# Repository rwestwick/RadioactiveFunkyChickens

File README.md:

# RadioactiveFunkyChickens

These are the Python files for the RadioactiveFunkyChickens team's PiWars robot.

## Files

### Challenge code

- LineFollowingAlgorithm.py: Code for the [line following challenge] (http://piwars.org/2017-competition/challenges/line-following/)
- MinimalMazeAlgorithm.py: Code for the [Minimal Maze challenge (http://piwars.org/2017-competition/challenges/minimal-maze/)
- straightLineSpeedTest2.py: Code for the [straight line speed test challenge] (http://piwars.org/2017-competition/challenges/straight-line-speed-test/)
- WiimoteControllerNunchukEye.py: Remote controller code to the non-autonomous PiWars challenges. Needs Wiimote Nunchuck and can control the servos for pan and tilt.

### Initio code

Several of the Python files are downloaded from the 4tronix web site to work with the Initio and Robohat hardware.

## See Also

- [RadioactiveFunkyChickens Blog] (https://radioactivefunkychickens.wordpress.com/)
- [PiWars] (http://piwars.org/)
- [Raspberry Pi] (http://www.raspberrypi.org/)
- [4tronix Initio Home Page] (http://4tronix.co.uk/blog/?p=169)

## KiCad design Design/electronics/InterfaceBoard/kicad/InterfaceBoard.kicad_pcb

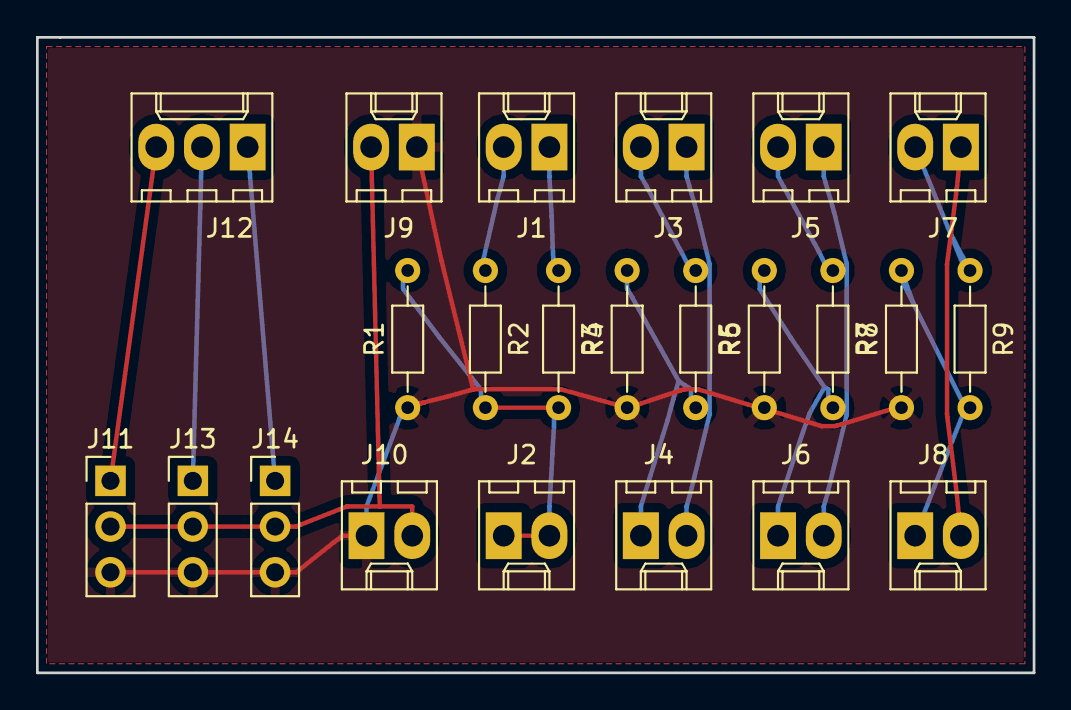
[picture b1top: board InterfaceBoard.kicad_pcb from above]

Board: 2 copper layers, 55.4 x 35.3 mm, 23 parts (0 on the bottom side), 17 nets.

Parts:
J1, J2: PROX1; Molex_KK-6410-02_02x2.54mm_Straight
J3, J4: PROX2; Molex_KK-6410-02_02x2.54mm_Straight
J5, J6: PROX3; Molex_KK-6410-02_02x2.54mm_Straight
J7, J8: PROX4; Molex_KK-6410-02_02x2.54mm_Straight
J9: PWR IN; Molex_KK-6410-02_02x2.54mm_Straight
J10: PWR OUT; Molex_KK-6410-02_02x2.54mm_Straight
J11: HORZ; Pin_Header_Straight_1x03_Pitch2.54mm
J12: SERVO_IN; Molex_KK-6410-03_03x2.54mm_Straight
J13: VERT; Pin_Header_Straight_1x03_Pitch2.54mm
J14: FIRE; Pin_Header_Straight_1x03_Pitch2.54mm
R1, R2, R5, R7, R9: 1k; R_Axial_DIN0204_L3.6mm_D1.6mm_P7.62mm_Horizontal
R3, R4, R6, R8: 2k2; R_Axial_DIN0204_L3.6mm_D1.6mm_P7.62mm_Horizontal

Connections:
+5V: J9.2, J10.2, J11.2, J13.2, J14.2
GND: J9.1, J10.1, J11.3, J13.3, J14.3, R1.1, R4.1, R6.1, R8.1
unnamed: J1.1, R3.1
unnamed: J1.2, R2.1
unnamed: J2.1, J2.2, R1.2, R2.2, R3.2
unnamed: J3.1, J4.2
unnamed: J3.2, R5.1
unnamed: J4.1, R4.2, R5.2
unnamed: J5.1, J6.2
unnamed: J5.2, R7.1
unnamed: J6.1, R6.2, R7.2
unnamed: J7.1, J8.2
unnamed: J7.2, R9.1
unnamed: J8.1, R8.2, R9.2
unnamed: J11.1, J12.3
unnamed: J12.1, J14.1
unnamed: J12.2, J13.1

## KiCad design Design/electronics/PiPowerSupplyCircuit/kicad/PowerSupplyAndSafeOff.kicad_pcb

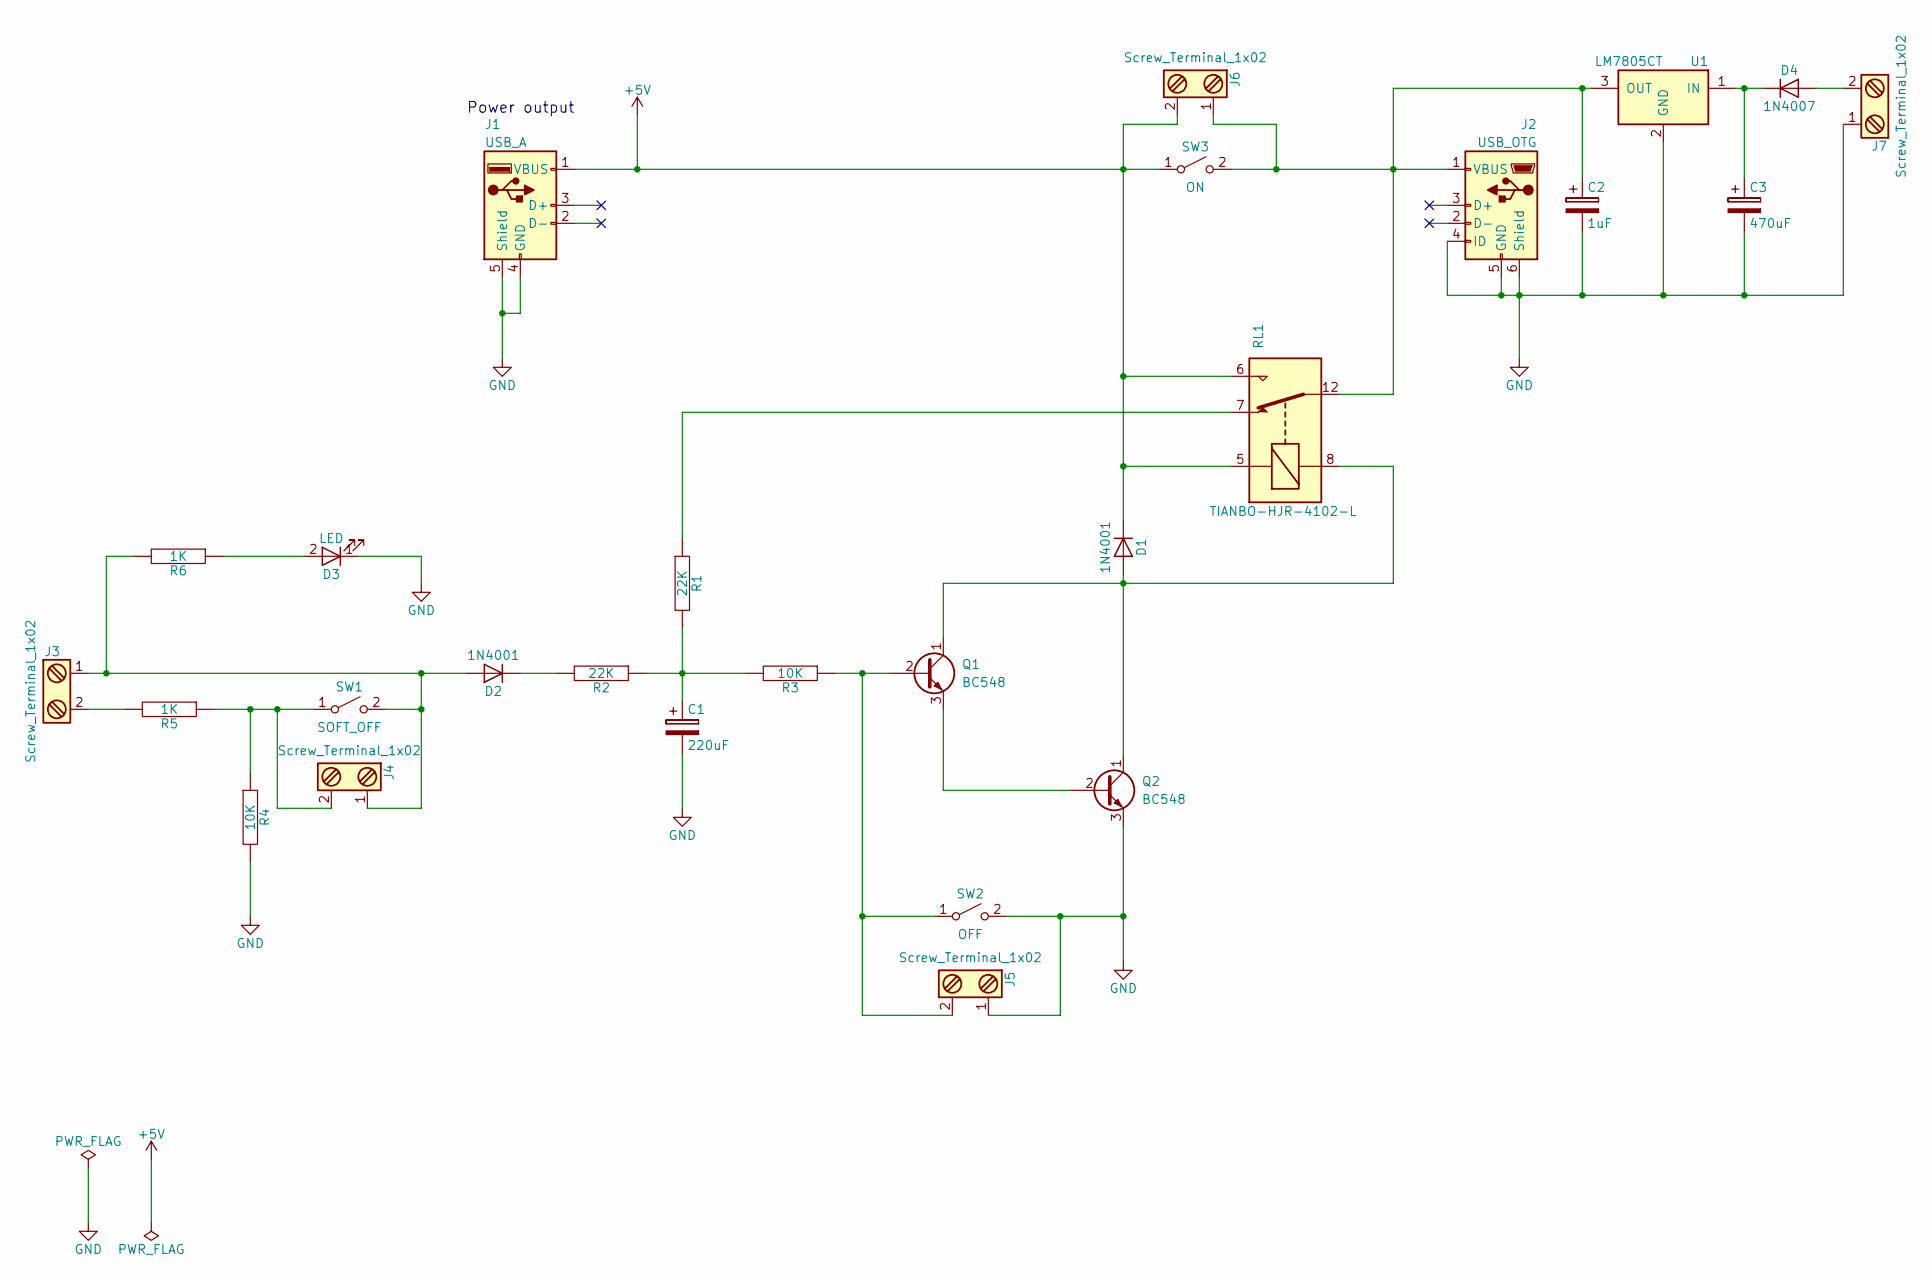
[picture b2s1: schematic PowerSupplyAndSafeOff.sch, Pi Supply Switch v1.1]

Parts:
C1: 220uF; CP_Radial_D5.0mm_P2.50mm
C2: 1uF; CP_Radial_D5.0mm_P2.50mm
C3: 470uF; CP_Radial_D5.0mm_P2.50mm
D1, D2: 1N4001; D_T-1_P10.16mm_Horizontal
D3: LED; LED_D3.0mm
D4: 1N4007; D_T-1_P10.16mm_Horizontal
J1: USB_A
J2: USB_OTG; USB_Micro-B
J3, J4, J5, J6, J7: Screw_Terminal_1x02; PhoenixContact_MC-G_02x5.08mm_Angled
Q1, Q2: BC548; TO-92_Inline_Narrow_Oval
R1, R2: 22K; R_Axial_DIN0207_L6.3mm_D2.5mm_P7.62mm_Horizontal
R3, R4: 10K; R_Axial_DIN0207_L6.3mm_D2.5mm_P7.62mm_Horizontal
R5, R6: 1K; R_Axial_DIN0207_L6.3mm_D2.5mm_P7.62mm_Horizontal
RL1: TIANBO-HJR-4102-L; Relay_SPDT_HJR-4102
SW1: SOFT_OFF; SW_PUSH_6mm_h4.3mm
SW2: OFF; SW_PUSH_6mm_h4.3mm
SW3: ON; SW_PUSH_6mm_h4.3mm
U1: LM7805CT; TO-220

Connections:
+5V: D1.1 (K), J1.1 (VBUS), J6.2, RL1.5, RL1.6, SW3.1 (A)
GND: C1.2, C2.2, C3.2, D3.1 (K), J1.4 (GND), J1.5 (Shield), J2.4 (ID), J2.5 (GND), J2.6 (Shield), J5.1, J7.1, Q2.3 (E), R4.2, SW2.2 (B), U1.2 (GND)
unnamed: C1.1, R1.2, R2.1, R3.2
unnamed: C2.1, J2.1 (VBUS), J6.1, RL1.12, SW3.2 (B), U1.3 (OUT)
unnamed: C3.1, D4.1 (K), U1.1 (IN)
unnamed: D1.2 (A), Q1.1 (C), Q2.1 (C), RL1.8
unnamed: D2.1 (K), R2.2
unnamed: D2.2 (A), J3.1, J4.1, R6.2, SW1.2 (B)
unnamed: D3.2 (A), R6.1
unnamed: D4.2 (A), J7.2
unnamed: J3.2, R5.2
unnamed: J4.2, R4.1, R5.1, SW1.1 (A)
unnamed: J5.2, Q1.2 (B), R3.1, SW2.1 (A)
unnamed: Q1.3 (E), Q2.2 (B)
unnamed: R1.1, RL1.7

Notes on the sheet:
Power output

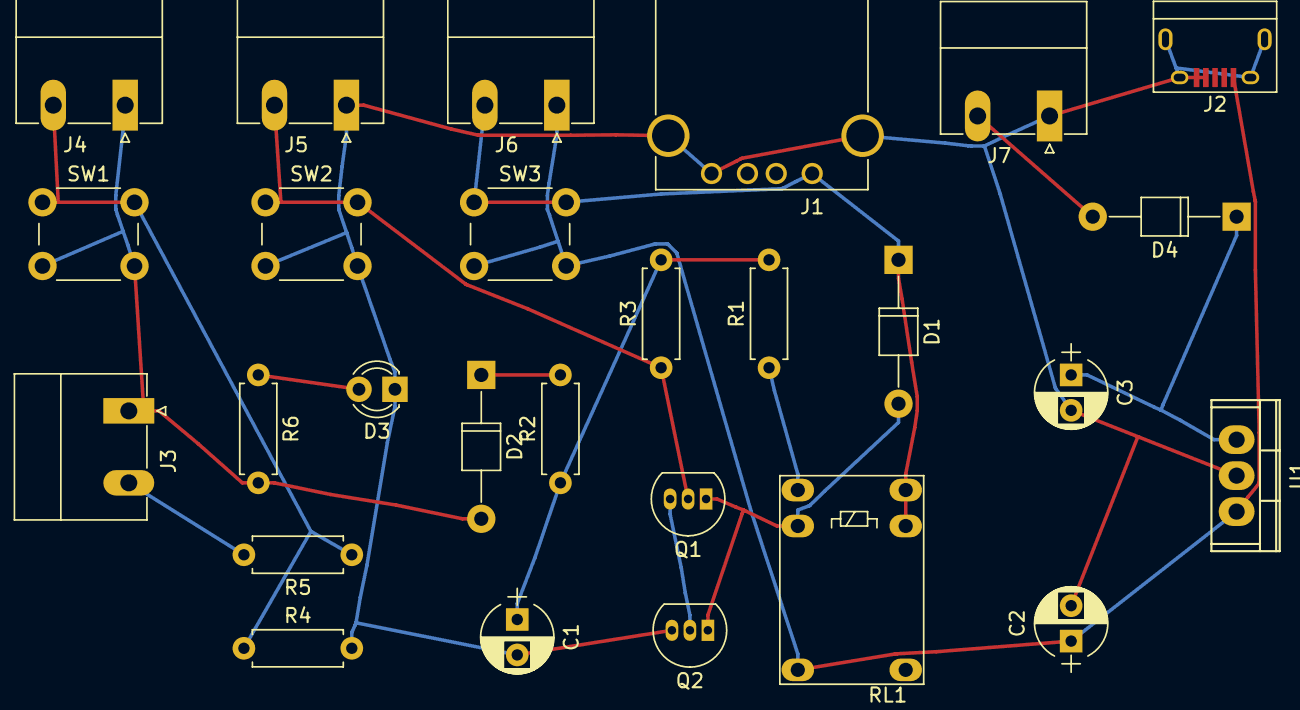
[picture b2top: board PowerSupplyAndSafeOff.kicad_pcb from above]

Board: 2 copper layers, 27 parts (0 on the bottom side), 15 nets.

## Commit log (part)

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2017-02-07 Fixed issues with code following being able to actually run it!
2017-02-07 Moved comment Measurement function to a docstring
2017-02-07 Fixed issues with the LineFollerSensor
2017-02-07 Fixed issues with the ServoController
2017-02-07 Added a one wheel turn (left and right) to the MotorController
2017-02-07 added +x to servod binary
2017-02-08 Made code pep8 compliant using flake8 IRSensor.py LineFollowerSensor.py MotorController.py ServoController.py UltrasonicSensor.py and pylint -f colorized -r no IRSensor.py LineFollowerSensor.py Motor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
2017-02-15 Split out the keyboard key reader into a separate file
2017-02-18 Adding pep8, pylint script for jenkins
2017-02-18 Updated line endings and access rights
2017-02-18 Added pylint config file and updated jenkins script to use it
2017-02-19 Added gitignore file with the pyc files as a starter
2017-02-19 Modified straight line speed test to use the new sensor and controller modules
2017-02-19 automatic code cleanup using autopep8 and autoflake
2017-02-19 updated cloc script to count all file types and not just python
2017-02-19 code tidyup
2017-02-19 Added install files and pycharm files
2017-02-19 initialised the motor controller with the pins from the new python file
2017-02-19 Updated line follower algo code
2017-02-19 fixed old sonarrfc reference in straight line speed test
2017-02-19 updated speed to use the motor contorller defines
2017-02-19 Updated Line following algo
2017-02-19 Brought the line following algo in line with the little robot
2017-02-19 fixed pep8 issue and moved additional file to test folder
2017-02-19 More pep8 changes. Now ignoring issues in the test folder
2017-02-19 converted to unix crlf
2017-02-25 Correct straightLineSpeedTest2 angle rounding.
2017-02-25 Converted to unix line endings
2017-02-25 Corrected variable name
2017-02-25 more debugging
2017-02-25 reduced times in motor controller test
2017-02-26 Adding servod to folder.
2017-02-26 Corrected comment and made correction times a constant variable.
2017-02-27 Added function variable detail in wallAngle function.
2017-02-28 Track direction variable.
2017-02-28 Changing speed variable automatically applied to current direction.
2017-03-04 Added program to start testing line detection using RaspberryPi camera.
2017-03-04 Updated camera line follower
2017-03-05 Added comments to clarify what each of the function parameters are.
2017-03-05 Added more detail in comments.
2017-03-07 Line testing now working across all rows.
2017-03-08 Generating error on buffer length.
2017-03-11 Not an object, but a functional algorithm for line following.
2017-03-11 Updated algorithm and removed small bug.
2017-03-11 Removed small test code as no longer needed.
2017-03-11 Updated gpio and line sensor settings
2017-03-14 Starting minimal maze algorithm.
2017-03-15 Will this work?
2017-03-15 Adding untested Wiimote controller.
2017-03-18 Reduced timeouts in motor controller test
2017-03-18 Fixed some bugs.
2017-03-18 Minimal maze algo changes
2017-03-18 Robot travels around a box
2017-03-20 Turning check and small updates to the minimal maze algo
2017-03-29 Updated controller to work better in Pi Noon.
2017-04-01 Using Nunchuck.
2017-04-01 Using Nunchuck for slow and fast.
2017-04-01 speeds changed in the line follower
2017-04-04 Updated servi controller code.
2017-04-06 Script needed to start Python VM on some OpenCV installations.
2017-04-06 Needed to add extra comment line.
2017-04-08 Increase accuracy of speed and added turning right and left.
2017-04-09 Updated to include algorithms used in the competition.
2017-04-24 Test for all sensors in v7.
2017-04-24 Updated to include all sensors.
2017-04-29 .has_key() was deprecated so used 'in'
2017-10-27 First pass on red color detection code.
2017-10-29 Working out left and right on 2x2 grid.
2017-10-29 Commiting file.
2017-11-11 Added ability to switch a gpio port on and off
2017-11-11 Updated for Duckshoot algorithm
2017-11-11 Created from new respository.
2017-11-11 Updated ServoController to use the update sevod commands
2017-11-12 Corrected so that all p1 and added echo to command line.
2017-11-12 Fixed bugs, but pan angle still not zeroed correctly.
2017-11-14 Removed print from echo string as not needed for testing purposes.
2017-11-14 Added matrix calculation.
2017-11-15 Added HSV ranges.
2017-11-16 Can rotate through colour selector ranges.
2017-11-17 Added some YUV colour conversation.
2017-11-18 Added key to capture relevant frames to image (.png) files.
2017-11-20 Added output of HSV mask in RGB and printed picture.
2017-11-21 Added additional red detection for less than 0 deg.
2017-11-24 Finds largest contour and puts a white dot in the middle.
2017-11-25 Fixed bug on largest contour, but still errors.
2017-11-26 Added histogram, though using matplotlib causes video to freeze.
2017-11-26 added new controller algo
2017-11-26 Small changes.
2017-11-26 Added Dual Motor driver controller Fixed gpio to match the correct wheels Updated dual motor tester programme
2017-11-26 Added movement videos
2017-11-26 added one wheel movements to dual driver test
2017-12-02 Adding basic turning and speed algorithms, but with no motor control.
2017-12-03 Added initial servo centering.
2017-12-09 Added circularity downselection.
2017-12-10 Set initial pan and tilt values through testing. Shows pan and tilt values in video while setting.
2017-12-10 Extended range of red for hue values to left of 0 and increased sensitivity of all ranges.
2017-12-15 Added basic motor control for testing with one marker.
2017-12-17 fixed issues with the various levels of motorcontrollers. also noticed the gpio pins not set correctly. added another motor test function
2017-12-17 added video of new motor performance
2017-12-18 Changed code as speed settings now in SpeedSettings.
2017-12-22 Updating code to filter out noise.
2017-12-22 Adding Colour Boundary contants.
2017-12-23 Working through some more pep8 changes.
2017-12-24 Breaking algorithm into seperate functions.
2017-12-24 Broke down main() into separate functions.
2017-12-24 Fixed some pep8 and pylint
2017-12-24 auto pep8 fixes
2017-12-25 updated auto checking and ran autopep8 script again
2017-12-25 pep8 and flake8 fixes
2017-12-25 added pep8ify to list of scripts to run to correct formatting ran the updated autopep8 script
2017-12-25 changing to a more pythonesque return
2017-12-26 Added ability to run coverage tests on motor controllers
2017-12-26 Added ultrasonic interface to unit and coverage tests
2017-12-26 added missing file
2017-12-26 fixed missing import
2017-12-26 Added new test to list
2017-12-26 fixed warnings
2017-12-26 Fixed more warnings
2017-12-26 Added 2 new tests
2017-12-26 Added Servo controller tests
2017-12-27 Added values and function for YUV colourscape. Values need refining.
2017-12-28 Fixed a few more warnings
2017-12-28 fixed a few typos in comments
2018-01-03 Updated to include more class details.
2018-01-03 Code working, but image static.
2018-01-03 Code working, but still image static.
2018-01-04 Further updates.
2018-01-04 Added motor steering function & image processing time.
2018-01-04 added wiimote install command
2018-01-05 Small changes
2018-01-05 Fixed bug in no contours and added processing time calculation.
2018-01-06 Reduced resolution and changed variable naming.
2018-01-06 fixed gpio switching following some testing on the pi
2018-01-08 Capitolisation of a folder
2018-01-08 consistent rwx flags
2018-01-08 added servo veroboard required to connect to the pi when there isnt a robothat in the middle
2018-01-08 added new test to show multiple ultrasonic instances
2018-01-09 Fixed random default variable that didnt belong in this class
2018-01-09 Added ability to turn on more detailed debug logging
2018-01-09 added colorlog to the install script
2018-01-09 Added front ultrasonic thread measurement.
2018-01-09 fixed typos in comments and remove explicit call to __Del__() as this is not required
2018-01-12 Updated install scripts following image rebuild
2018-01-13 Updated schematic
2018-01-13 updated log output
2018-01-13 updated install script
2018-01-13 Updated ultrasonic test outputs
2018-01-14 added battery dimensions
2018-01-14 Added larger battery to smaller chassis.
2018-01-16 Added 60mm mecanum wheels.
2018-01-16 Added two 5 x AA battery holders.
2018-01-18 Updated with correct ultrasonic mounts & holes.
2018-01-23 Updated StraightLineSpeedTestAlgorithm.py to use the dual motor configuration Added turn_forward and turn_reverse to the dual motor controller Added tests for new dual motor controller functions Upda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
2018-01-28 added 6v motor brackets
2018-01-28 First pass at Nerf Gun mount.
2018-02-03 Added wiring image for L298N motor controller
2018-02-03 Updated Motor Wiring diagram
2018-02-05 First pass on deranged golf attachment/addition.
2018-02-10 Added GPIO image and component diagram
2018-02-10 ran autoped8 script
2018-02-11 Initialise pan/tilt servo angles.
2018-02-12 First draft as separate file.
2018-02-12 Speed and direction function added.
2018-02-24 Nick's additions.
2018-02-24 Added power supply circuit, veraboard and pcb design
2018-02-24 more moving of directories
2018-02-24 deleted backup file
2018-02-24 moved an image of the pcb to the top level folder
2018-02-24 added image of interface board pcb
2018-02-25 Updated to new imports.
2018-02-25 Changed constants after testing.
2018-03-01 Works it's way through colours!
2018-03-03 Made debug comments more explicit.
2018-03-03 Linked to GPIOLayout.py & chose pin for DuckShoot.
2018-03-04 Duck shoot changes to electronics design
2018-03-04 Updated to use Nerf Gun holder.
2018-03-04 Added RS order list
2018-03-04 Updated the veroboard circuits Updated the interface board design updated the RS parts list
2018-03-05 Fixed compile issue and missing logging
2018-03-06 Created a common wiimote controller interface and updated the duck shoot algorithm to use it. Modified the gpio handling to use a different gpiozero library as this allowed me to read the state back.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
2018-03-06 added debug t oservo controller
2018-03-07 updated servod with latest code. Updated servo test to also test the nerf servo
2018-03-07 updated alternate gpiozero library servo test
2018-03-07 Updated isntall script with pip versions of apt installs required for 14.4
2018-03-07 moved alternate servo test file as not going to be used
2018-03-07 Got the Duck shoot algorithm and associated code working!
2018-03-07 Moved old files into test area
2018-03-07 fixed sleeps to be infiniate rather than limited in the jusdt drive and duck shoot algos
2018-03-08 Heavilly refactored the somewhere over the rainbow code
2018-03-08 Moved the old somewhere over the rainbow file into the test area
2018-03-08 Ran the autopep8 script
2018-03-09 Updated CameraThread as a precurser to the over the rainbow in order to de-couple the logic further
2018-03-09 Fixed random reverse at the start of anything using the wiimote interface
2018-03-09 Fixed issue with the pan and tilt getting mixed up.
2018-03-10 Finishined moving somewhere over the rainbow code.
2018-03-11 Update to Slightly Deranged Golf design.
2018-03-15 Needed for Servo calculations.
2018-03-25 Fixed typos in the gpio controller
2018-03-26 added limits and offsets to the servos via a config file
2018-03-26 allowed servo tests to work on linux jenkins server
2018-03-27 Added file to initialise all of the interfaces used by the robot on system start-up
2018-03-27 Ran autopep8
2018-04-08 pep8 updates
2018-04-08 Fixed file typos
2018-04-08 For initial statup by adding a servo timeout
2018-04-08 updated servo config to apply pan offset
2018-04-08 added further delays to initialisation
2018-04-12 Added first draft for Nerf Holder mounting.
2018-04-15 Added new line break
2018-04-21 added web Links updated design files
